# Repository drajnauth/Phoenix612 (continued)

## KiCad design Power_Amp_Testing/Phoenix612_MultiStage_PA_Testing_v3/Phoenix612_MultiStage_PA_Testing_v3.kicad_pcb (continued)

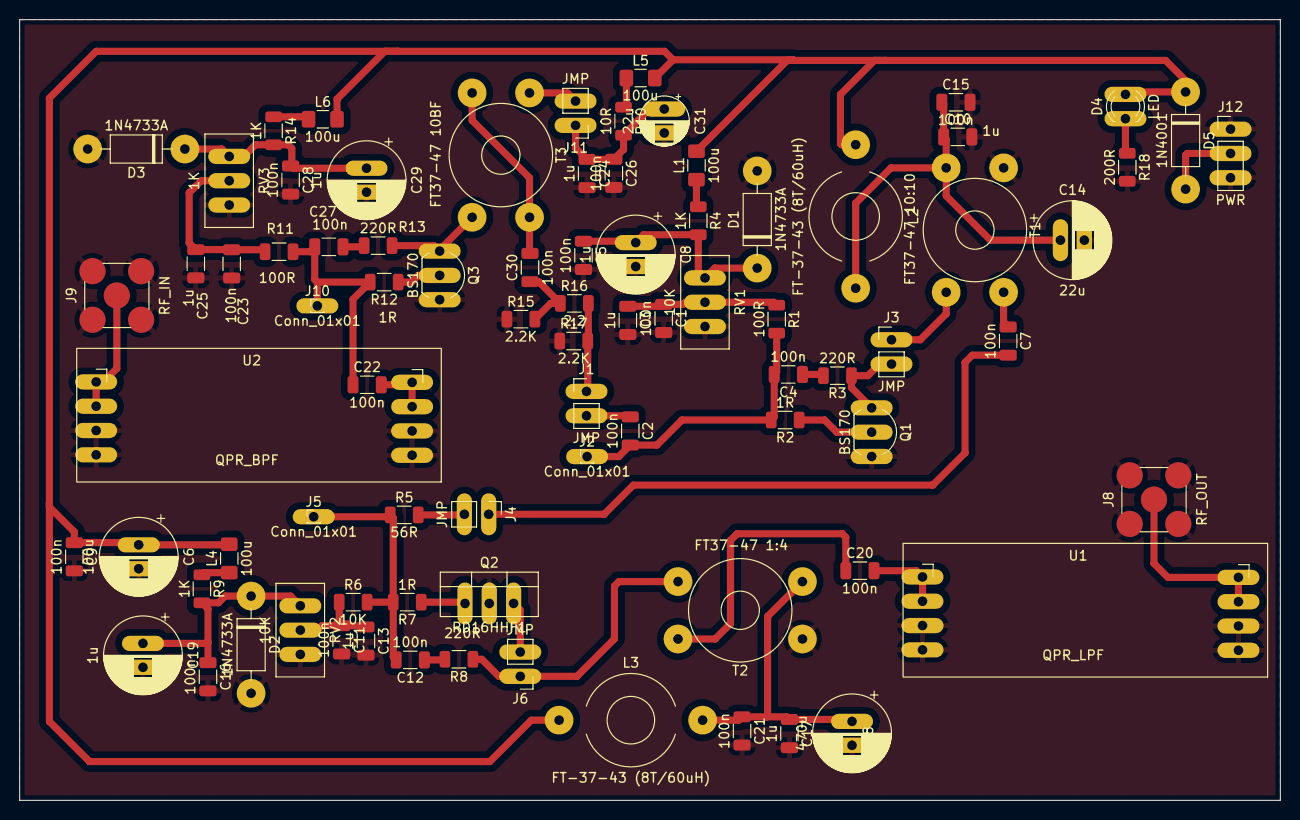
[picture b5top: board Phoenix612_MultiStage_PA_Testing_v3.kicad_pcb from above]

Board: 2 copper layers, 131.8 x 81.6 mm, 82 parts (0 on the bottom side), 44 nets.

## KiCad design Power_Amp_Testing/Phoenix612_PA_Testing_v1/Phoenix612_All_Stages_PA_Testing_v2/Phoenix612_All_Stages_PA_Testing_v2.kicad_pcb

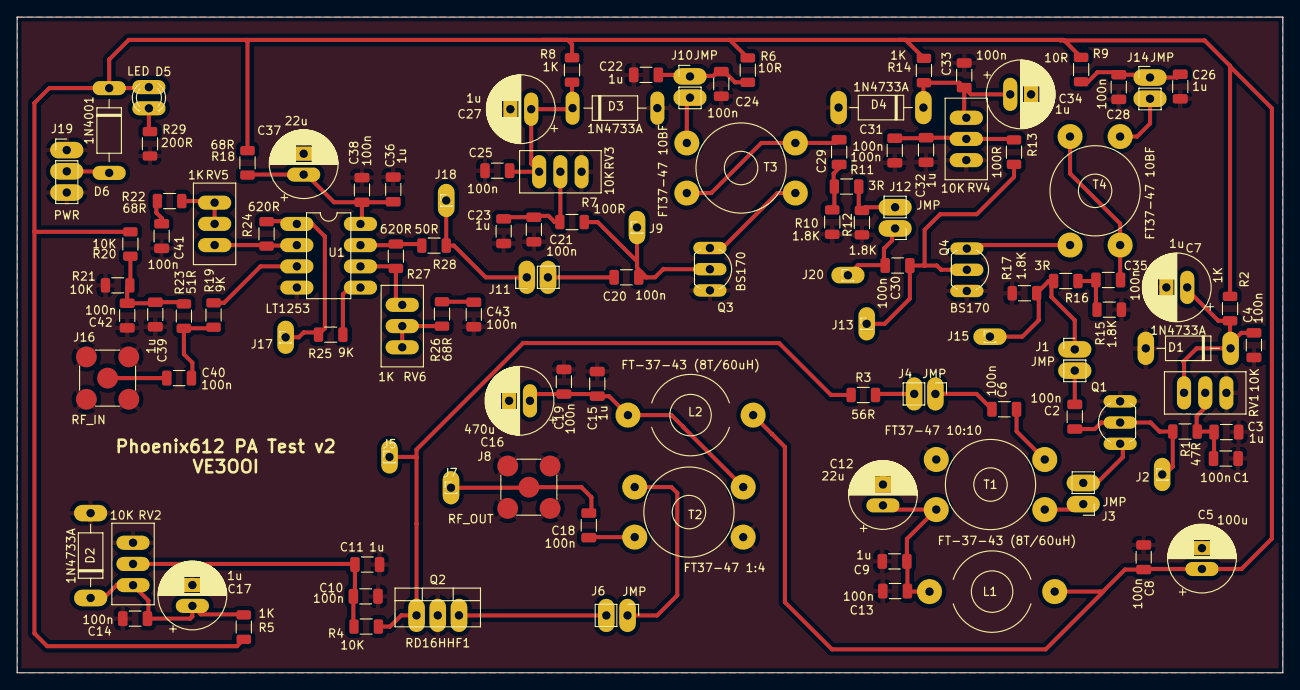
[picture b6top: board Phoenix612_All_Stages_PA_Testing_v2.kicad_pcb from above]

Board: 2 copper layers, 151.7 x 78.6 mm, 115 parts (0 on the bottom side), 57 nets.

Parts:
C1, C2, C4, C6, C8, C10, C13, C14, C18, C19, C20, C21, C24, C25, C28, C29, C30, C31, C33, C35, C38, C40, C41, C42, C43: 100n; C_1206_3216Metric
C3, C9, C11, C15, C22, C23, C26, C32, C36, C39: 1u; C_1206_3216Metric
C5: 100u; CP_Radial_D8.0mm_P2.50mm
C7, C17, C27, C34: 1u; CP_Radial_D8.0mm_P2.50mm
C12, C37: 22u; CP_Radial_D8.0mm_P2.50mm
C16: 470u; CP_Radial_D8.0mm_P2.50mm
D1, D2, D3, D4: 1N4733A; D_DO-41_SOD81_P10.16mm_Horizontal
D5: LED; LED_D3.0mm
D6: 1N4001; D_DO-41_SOD81_P10.16mm_Horizontal
J1, J3, J4, J6, J10, J11, J12, J14: JMP; PinHeader_1x02_P2.54mm_Vertical
J2, J5, J7, J9, J13, J15, J17, J18, J20: Conn_01x01; PinHeader_1x01_P1.00mm_Vertical
J8: RF_OUT; SMA_Amphenol_901-144_Vertical
J16: RF_IN; SMA_Amphenol_901-144_Vertical
J19: PWR; PinHeader_1x03_P2.54mm_Vertical
L1, L2: FT-37-43 (8T/60uH); L_Toroid_Horizontal_D9.5mm_P15.00mm_Diameter10-5mm_Amidon-T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
Q1, Q3, Q4: BS170; TO-92_Inline_Wide
Q2: RD16HHF1; TO-220-3
R1: 47R; R_1206_3216Metric
R2, R5, R8, R14: 1K; R_1206_3216Metric
R3: 56R; R_1206_3216Metric
R4, R20, R21: 10K; R_1206_3216Metric
R6, R9: 10R; R_1206_3216Metric
R7, R13: 100R; R_1206_3216Metric
R10, R12, R15, R17: 1.8K; R_1206_3216Metric
R11, R16: 3R; R_1206_3216Metric
R18, R22, R26: 68R; R_1206_3216Metric
R19, R25: 9K; R_1206_3216Metric
R23: 51R; R_1206_3216Metric
R24, R27: 620R; R_1206_3216Metric
R28: 50R; R_1206_3216Metric
R29: 200R; R_1206_3216Metric
RV1, RV2, RV3, RV4: 10K; Potentiometer_Bourns_3296W_Vertical
RV5, RV6: 1K; Potentiometer_Bourns_3296W_Vertical
T1: FT37-47 10:10; Transformer_Toroid_Horizontal_D10.5mm_Amidon-T37
T2: FT37-47 1:4; Transformer_Toroid_Horizontal_D10.5mm_Amidon-T37
T3, T4: FT37-47 10BF; Transformer_Toroid_Horizontal_D10.5mm_Amidon-T37
U1: LT1253; DIP-8_W7.62mm

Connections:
DRIVER_IN: J11.1, J18.1, R28.2
GND: C1.2, C3.2, C4.2, C5.2, C7.2, C8.2, C9.2, C10.2, C11.2, C12.2, C13.2, C14.2, C15.2, C16.2, C17.2, C19.2, C21.2, C22.2, C23.2, C24.2, C25.2, C26.2, C27.2, C28.2, C31.2, C32.2, C33.2, C34.2, C36.2, C37.2, C38.2, C39.2, C41.2, C42.2, C43.2, D1.2 (A), D2.2 (A), D3.2 (A), D4.2 (A), J8.2 (Ext), J16.2 (Ext), J19.1, J19.3, Q1.3 (S), Q2.2, Q3.3 (S), Q4.3 (S), R10.1, R12.1, R15.1, R17.1, R21.2, R29.2, RV1.1, RV2.1, RV3.1, RV4.1, T1.3 (SB), T2.3 (SB), U1.4 (V-)
M1_12V: C9.1, C12.1, C13.1, L1.2, T1.1 (AA)
M2_12V: C15.1, C16.1, C19.1, L2.2, T2.1 (AA)
unnamed: C1.1, C3.1, R1.1, RV1.2
unnamed: C2.1, J1.2
unnamed: C2.2, J2.1, Q1.2 (G), R1.2
unnamed: C4.1, C7.1, D1.1 (K), R2.2, RV1.3
unnamed: C6.1, T1.4 (SA)
unnamed: C6.2, J4.1
unnamed: C10.1, C11.1, R4.1, RV2.2
unnamed: C14.1, C17.1, D2.1 (K), R5.2, RV2.3
unnamed: C18.1, T2.4 (SA)
unnamed: C18.2, J7.1, J8.1 (In)
unnamed: C20.2, J11.2
unnamed: C21.1, C23.1, R7.1, RV3.2
unnamed: C25.1, C27.1, D3.1 (K), R8.2, RV3.3
unnamed: C29.1, R10.2, R11.1
unnamed: C29.2, T3.1 (AA), T3.4 (SA)
unnamed: C30.1, J13.1, Q4.2 (G), R13.2
unnamed: C30.2, J12.1, J20.1
unnamed: C31.1, C32.1, R13.1, RV4.2
unnamed: C33.1, C34.1, D4.1 (K), R14.2, RV4.3
unnamed: C35.1, R15.2, R16.1
unnamed: C35.2, T4.1 (AA), T4.4 (SA)
unnamed: C36.1, C37.1, C38.1, R18.2, U1.8 (V+)
unnamed: C39.1, C42.1, R20.2, R21.1, R23.2
unnamed: C40.1, J16.1 (In)
unnamed: C40.2, R19.1, R23.1
unnamed: C41.1, R22.2
unnamed: C43.1, R26.2
unnamed: D5.1 (K), R29.1
unnamed: D6.2 (A), J19.2
unnamed: J3.1, T1.2 (AB)
unnamed: J3.2, Q1.1 (D)
unnamed: J4.2, R3.2
unnamed: J5.1, Q2.1, R3.1, R4.2
unnamed: J6.1, T2.2 (AB)
unnamed: J6.2, Q2.3
unnamed: C20.1, J9.1, Q3.2 (G), R7.2
unnamed: J10.2, T3.3 (SB)
unnamed: J12.2, R11.2, R12.2
unnamed: J14.2, T4.3 (SB)
unnamed: J17.1, R24.2, R25.1, U1.1 (OutA)
unnamed: Q3.1 (D), T3.2 (AB)
unnamed: Q4.1 (D), T4.2 (AB)
unnamed: R19.2, U1.3 (InA+)
unnamed: R22.1, RV5.2, RV5.3
unnamed: R24.1, RV5.1, U1.2 (InA-)
unnamed: R25.2, U1.5 (InB+)
unnamed: R26.1, RV6.2, RV6.3
unnamed: R27.1, R28.1, U1.7 (OutB)
unnamed: R27.2, RV6.1, U1.6 (InB-)
PA_IN: J1.1, J15.1, R16.2, R17.2
Q1_12V: C22.1, C24.1, J10.1, R6.2
Q2_12V: C26.1, C28.1, J14.1, R9.2
TX12V: C5.1, C8.1, D5.2 (A), D6.1 (K), L1.1, L2.1, R2.1, R5.1, R6.1, R8.1, R9.1, R14.1, R18.1, R20.1

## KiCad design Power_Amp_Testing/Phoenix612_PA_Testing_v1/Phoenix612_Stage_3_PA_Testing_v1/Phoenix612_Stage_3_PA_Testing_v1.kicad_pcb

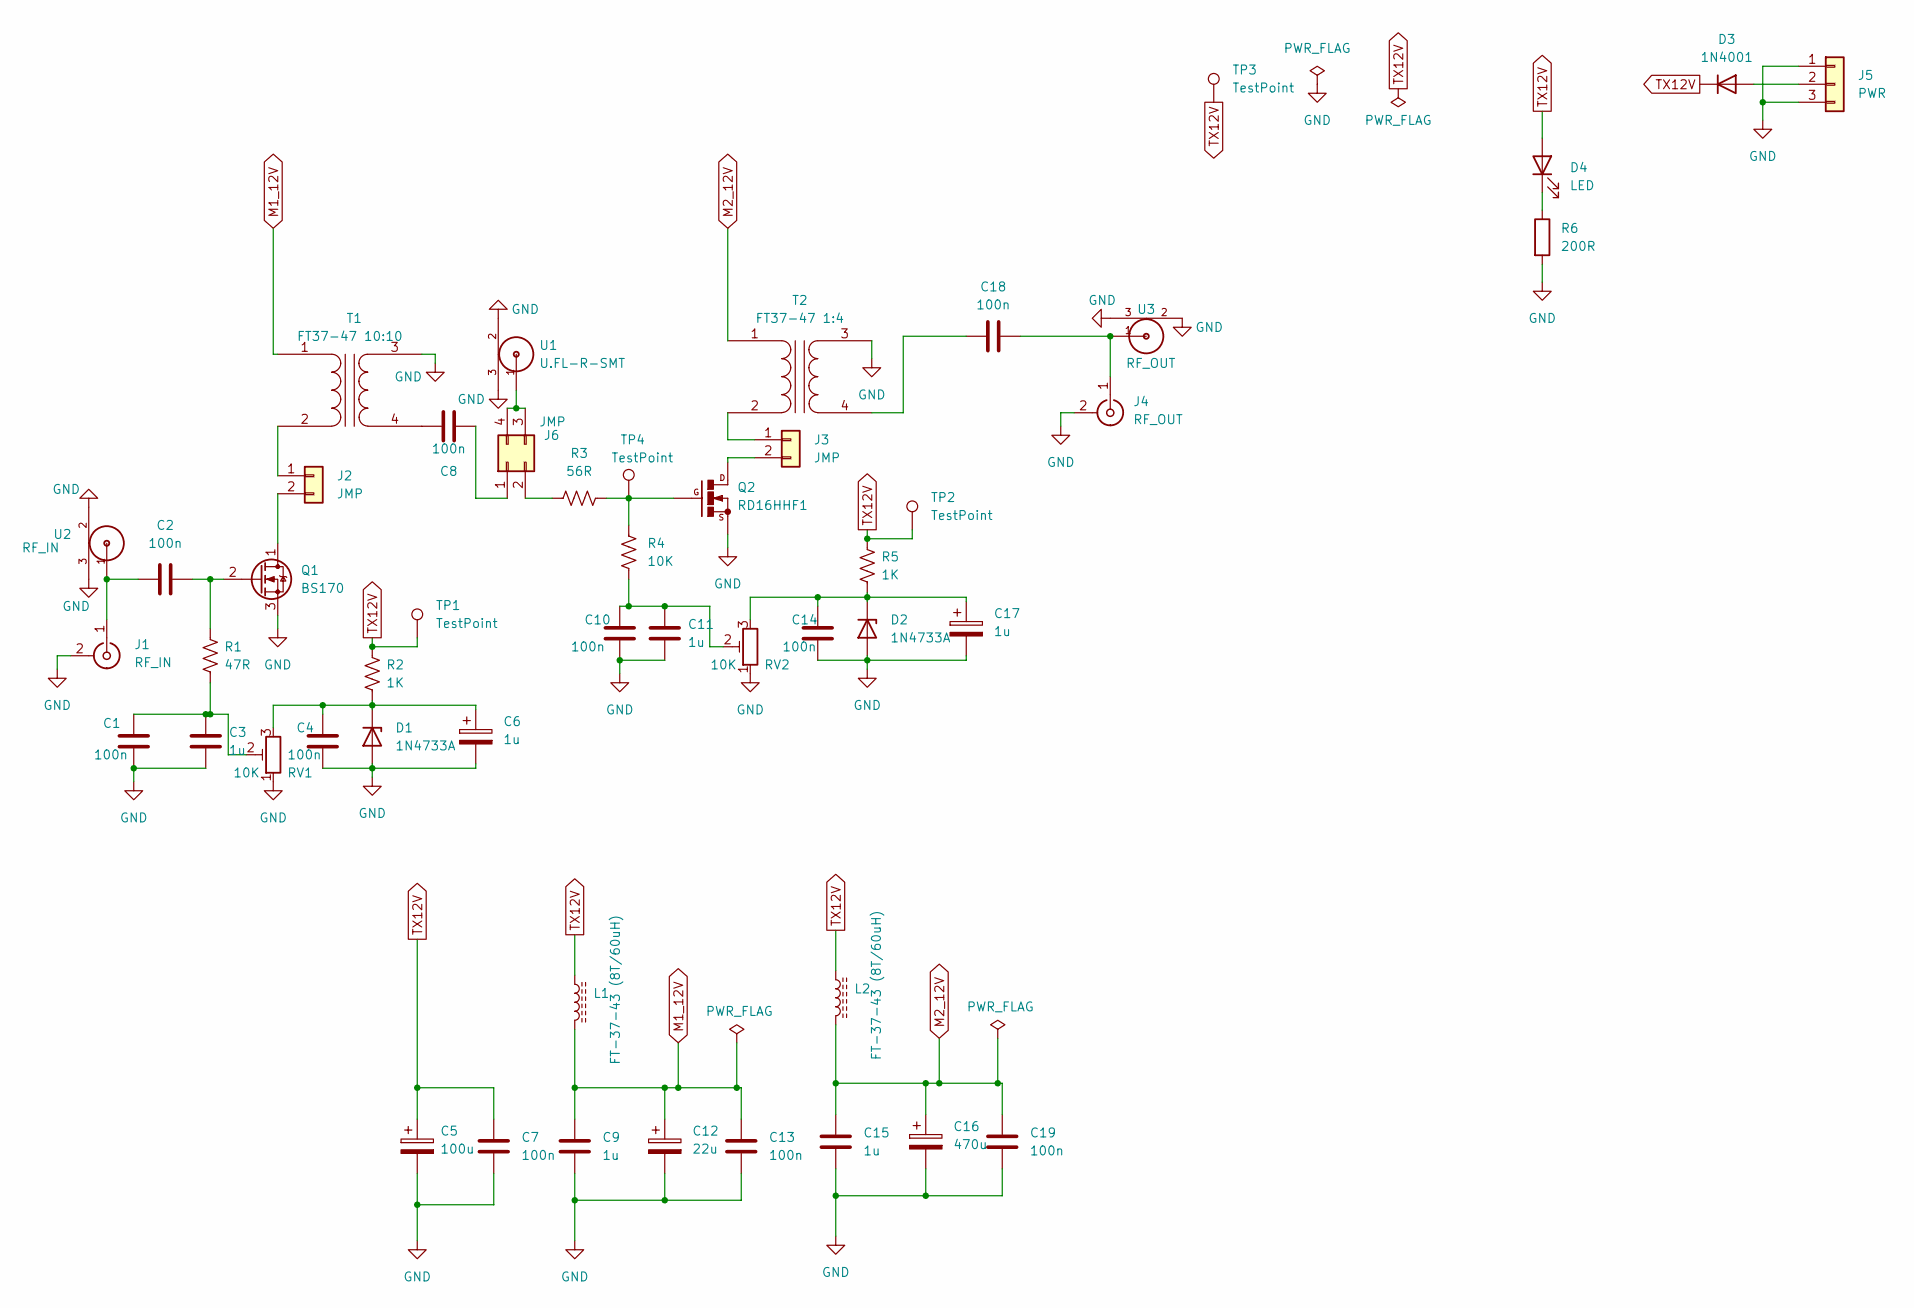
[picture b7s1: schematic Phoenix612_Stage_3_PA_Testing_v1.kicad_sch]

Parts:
C1, C2, C4, C7, C8, C10, C13, C14, C18, C19: 100n; C_1206_3216Metric
C3, C9, C11, C15: 1u; C_1206_3216Metric
C5: 100u; CP_Radial_D8.0mm_P2.50mm
C6, C17: 1u; CP_Radial_D8.0mm_P2.50mm
C12: 22u; CP_Radial_D8.0mm_P2.50mm
C16: 470u; CP_Radial_D8.0mm_P2.50mm
D1, D2: 1N4733A; D_DO-41_SOD81_P10.16mm_Horizontal
D3: 1N4001; D_DO-41_SOD81_P10.16mm_Horizontal
D4: LED; LED_D3.0mm
J1: RF_IN; SMA_Amphenol_901-144_Vertical
J2, J3: JMP; PinHeader_1x02_P2.54mm_Vertical
J4: RF_OUT; SMA_Amphenol_901-144_Vertical
J5: PWR; PinHeader_1x03_P2.54mm_Vertical
J6: JMP; PinHeader_2x02_P2.54mm_Vertical
L1, L2: FT-37-43 (8T/60uH); L_Toroid_Horizontal_D9.5mm_P15.00mm_Diameter10-5mm_Amidon-T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
Q1: BS170; TO-92_Inline
Q2: RD16HHF1; TO-220-3
R1: 47R; R_1206_3216Metric
R2, R5: 1K; R_1206_3216Metric
R3: 56R; R_1206_3216Metric
R4: 10K; R_1206_3216Metric
R6: 200R; R_1206_3216Metric
RV1, RV2: 10K; Potentiometer_Bourns_3296W_Vertical
T1: FT37-47 10:10; Transformer_Toroid_Horizontal_D10.5mm_Amidon-T37
T2: FT37-47 1:4; Transformer_Toroid_Horizontal_D10.5mm_Amidon-T37
TP1, TP2, TP3, TP4: TestPoint; Pin_D0.7mm_L6.5mm_W1.8mm_FlatFork
U1: U.FL-R-SMT
U2: RF_IN; U.FL-R-SMT
U3: RF_OUT; U.FL-R-SMT

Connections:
GND: C1.2, C3.2, C4.2, C5.2, C6.2, C7.2, C9.2, C10.2, C11.2, C12.2, C13.2, C14.2, C15.2, C16.2, C17.2, C19.2, D1.2 (A), D2.2 (A), J1.2 (Ext), J4.2 (Ext), J5.1, J5.3, Q1.3 (S), Q2.2, R6.2, RV1.1, RV2.1, T1.3 (SB), T2.3 (SB), U1.2, U1.3, U2.2, U2.3, U3.2, U3.3
M1_12V: C9.1, C12.1, C13.1, L1.2, T1.1 (AA)
M2_12V: C15.1, C16.1, C19.1, L2.2, T2.1 (AA)
unnamed: C1.1, C3.1, R1.1, RV1.2
unnamed: C2.1, J1.1 (In), U2.1
unnamed: C2.2, Q1.2 (G), R1.2
unnamed: C4.1, C6.1, D1.1 (K), R2.2, RV1.3
unnamed: C8.1, T1.4 (SA)
unnamed: C8.2, J6.1
unnamed: C10.1, C11.1, R4.1, RV2.2
unnamed: C14.1, C17.1, D2.1 (K), R5.2, RV2.3
unnamed: C18.1, T2.4 (SA)
unnamed: C18.2, J4.1 (In), U3.1
unnamed: D3.2 (A), J5.2
unnamed: D4.1 (K), R6.1
unnamed: J2.1, T1.2 (AB)
unnamed: J2.2, Q1.1 (D)
unnamed: J3.1, T2.2 (AB)
unnamed: J3.2, Q2.3
unnamed: J6.2, R3.2
unnamed: J6.3, J6.4, U1.1
unnamed: Q2.1, R3.1, R4.2, TP4.1
TX12V: C5.1, C7.1, D3.1 (K), D4.2 (A), L1.1, L2.1, R2.1, R5.1, TP1.1, TP2.1, TP3.1

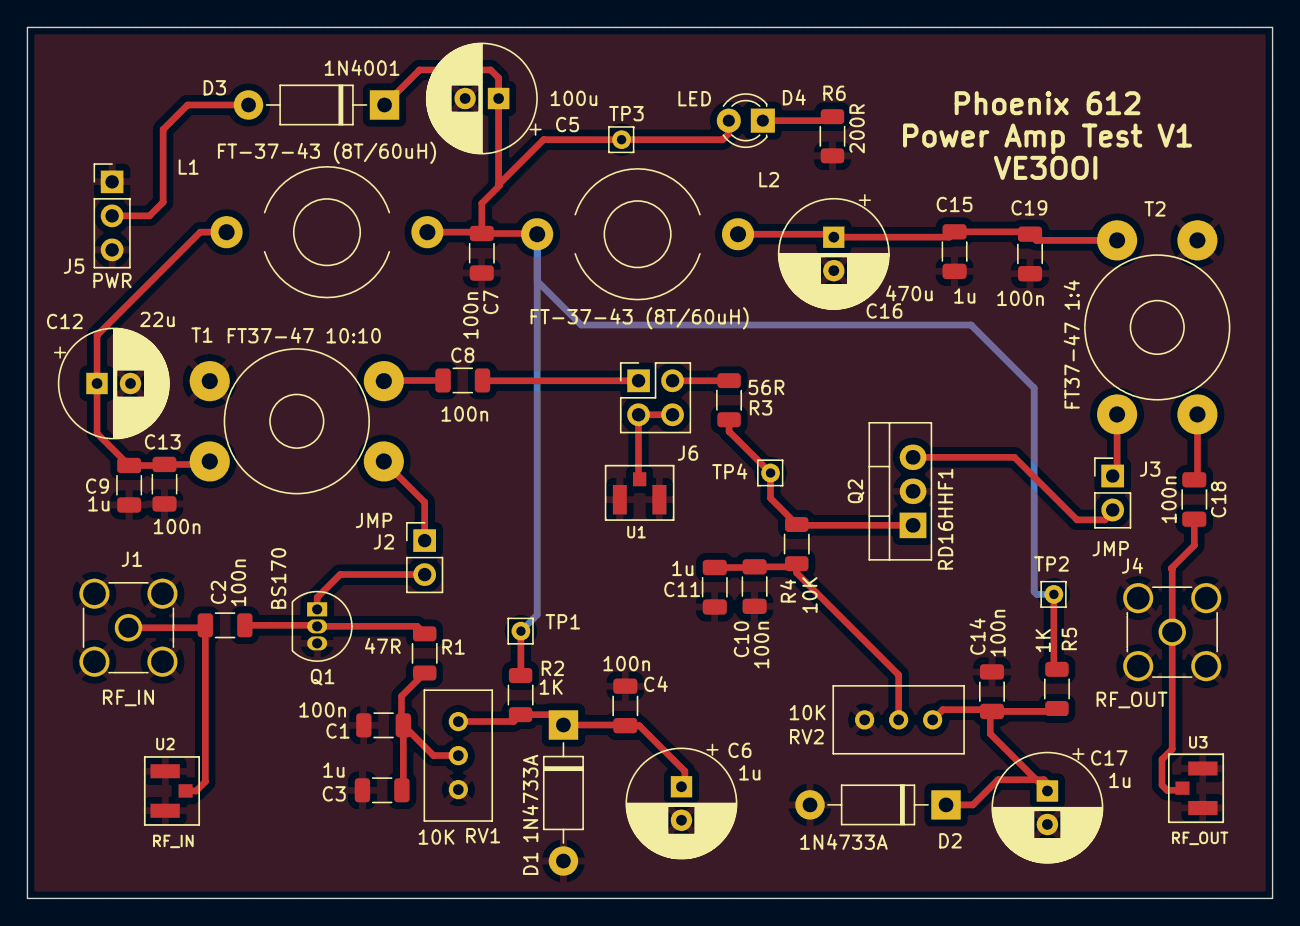
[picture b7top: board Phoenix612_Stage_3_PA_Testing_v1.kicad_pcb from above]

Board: 2 copper layers, 93.0 x 65.0 mm, 50 parts (0 on the bottom side), 23 nets.

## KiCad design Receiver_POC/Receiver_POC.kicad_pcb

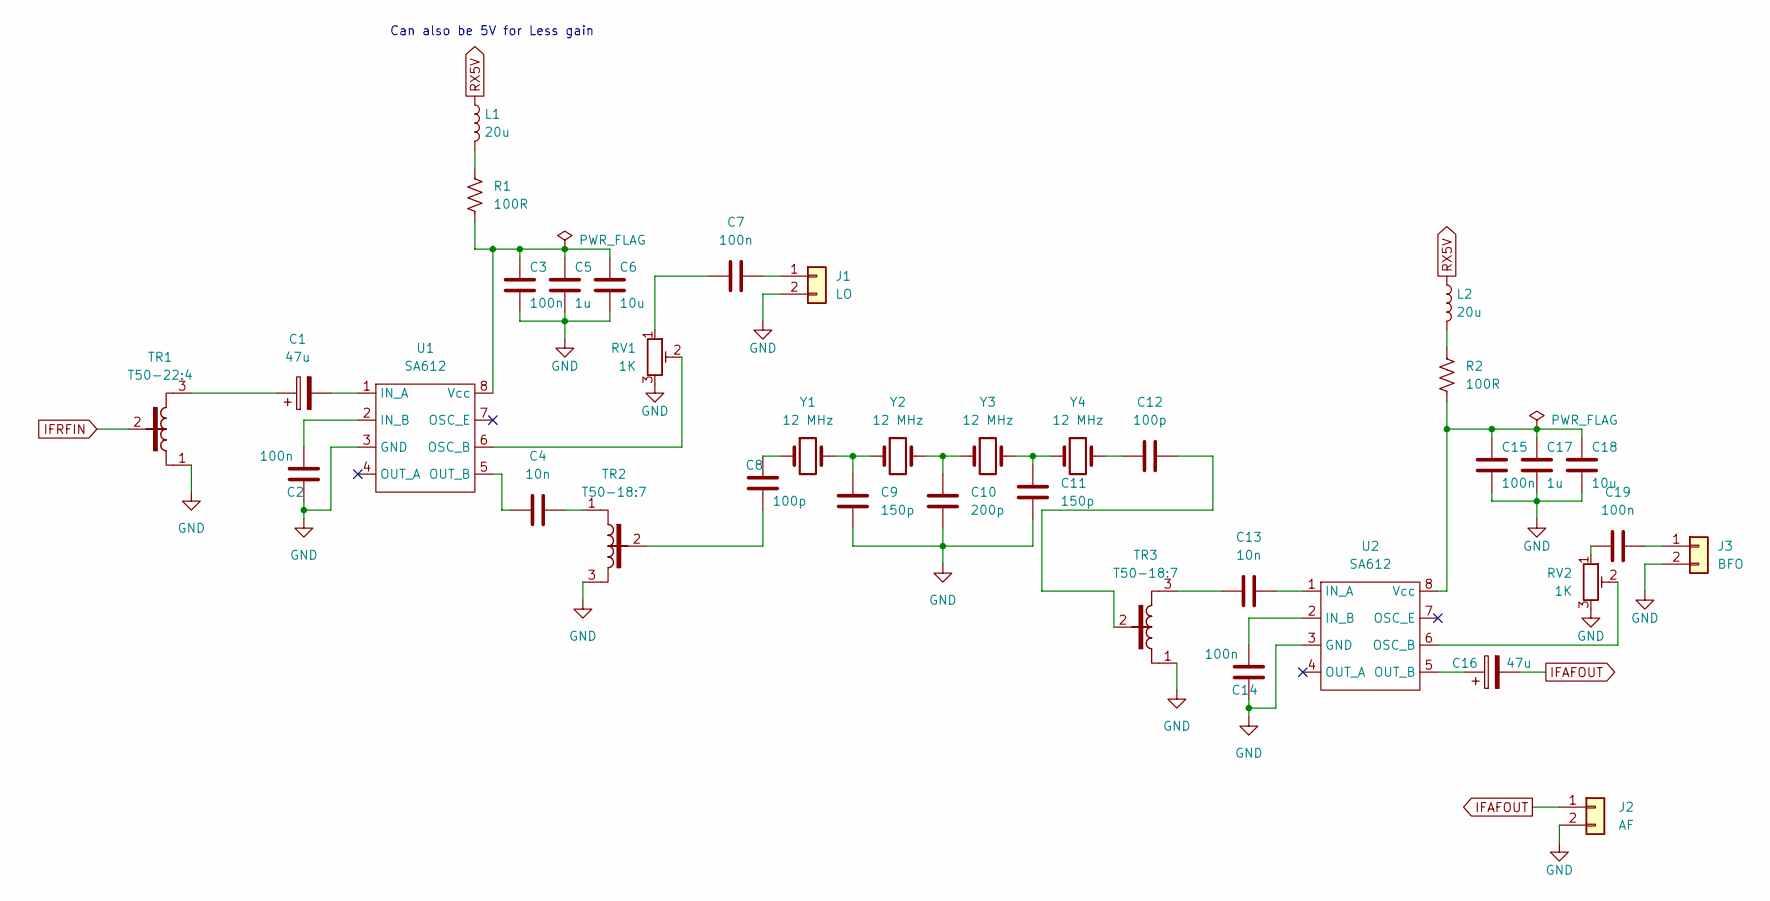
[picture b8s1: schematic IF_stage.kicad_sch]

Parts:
C1, C16: 47u; CP_Radial_D8.0mm_P2.50mm
C2, C3, C7, C14, C15, C19: 100n; C_1206_3216Metric
C4, C13: 10n; C_1206_3216Metric
C5, C17: 1u; C_1206_3216Metric
C6, C18: 10u; C_1206_3216Metric
C8, C12: 100p; C_Disc_D3.4mm_W2.1mm_P2.50mm
C9, C11: 150p; C_Disc_D3.4mm_W2.1mm_P2.50mm
C10: 200p; C_Disc_D3.4mm_W2.1mm_P2.50mm
J1: LO; PinHeader_1x02_P2.54mm_Vertical
J2: AF; PinHeader_1x02_P2.54mm_Vertical
J3: BFO; PinHeader_1x02_P2.54mm_Vertical
L1, L2: 20u; L_1206_3216Metric
R1, R2: 100R; R_1206_3216Metric
RV1, RV2: 1K; Potentiometer_Bourns_3296W_Vertical
TR1: T50-22:4; T50-1Tap-Close
TR2, TR3: T50-18:7; T50-1Tap-Close
U1, U2: SA612; DIP-8_W7.62mm_Socket
Y1, Y2, Y3, Y4: 12 MHz; Crystal_HC49-4H_Vertical

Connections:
GND: C2.2, C3.2, C5.2, C6.2, C9.2, C10.2, C11.2, C14.2, C15.2, C17.2, C18.2, J1.2, J2.2, J3.2, RV1.3, RV2.3, TR1.1, TR2.3, TR3.1, U1.3 (GND), U2.3 (GND); also elsewhere on the board
IFAFOUT: C16.2, J2.1
IFRFIN: TR1.2; also elsewhere on the board
unnamed: C1.1, TR1.3
unnamed: C1.2, U1.1 (IN_A)
unnamed: C2.1, U1.2 (IN_B)
unnamed: C3.1, C5.1, C6.1, R1.2, U1.8 (Vcc)
unnamed: C4.1, U1.5 (OUT_B)
unnamed: C4.2, TR2.1
unnamed: C7.1, J1.1
unnamed: C7.2, RV1.1
unnamed: C8.1, TR2.2
unnamed: C8.2, Y1.1
unnamed: C9.1, Y1.2, Y2.1
unnamed: C10.1, Y2.2, Y3.1
unnamed: C11.1, Y3.2, Y4.1
unnamed: C12.1, Y4.2
unnamed: C12.2, TR3.2
unnamed: C13.1, TR3.3
unnamed: C13.2, U2.1 (IN_A)
unnamed: C14.1, U2.2 (IN_B)
unnamed: C15.1, C17.1, C18.1, R2.2, U2.8 (Vcc)
unnamed: C16.1, U2.5 (OUT_B)
unnamed: C19.1, J3.1
unnamed: C19.2, RV2.1
unnamed: L1.2, R1.1
unnamed: L2.2, R2.1
unnamed: RV1.2, U1.6 (OSC_B)
unnamed: RV2.2, U2.6 (OSC_B)
RX5V: L1.1, L2.1; also elsewhere on the board

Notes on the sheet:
Can also be 5V for Less gain

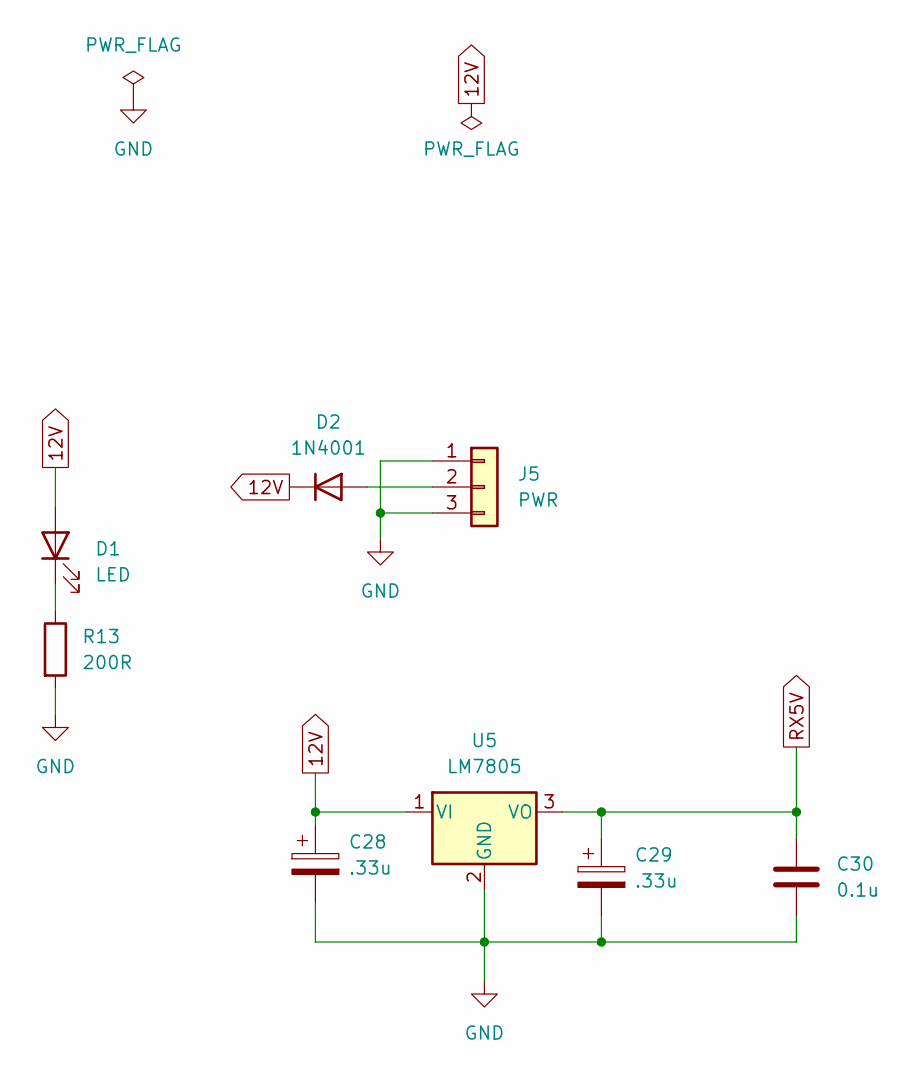
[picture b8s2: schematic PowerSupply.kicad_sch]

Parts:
C28, C29: .33u; CP_Radial_D8.0mm_P2.50mm
C30: 0.1u; C_1206_3216Metric
D1: LED; LED_D3.0mm
D2: 1N4001; D_DO-41_SOD81_P10.16mm_Horizontal
J5: PWR; PinHeader_1x03_P2.54mm_Vertical
R13: 200R; R_1206_3216Metric
U5: LM7805; TO-220-3_Vertical

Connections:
12V: C28.1, D1.2 (A), D2.1 (K), U5.1 (VI)
GND: C28.2, C29.2, C30.2, J5.1, J5.3, R13.2, U5.2 (GND); also elsewhere on the board
unnamed: D1.1 (K), R13.1
unnamed: D2.2 (A), J5.2
RX5V: C29.1, C30.1, U5.3 (VO); also elsewhere on the board

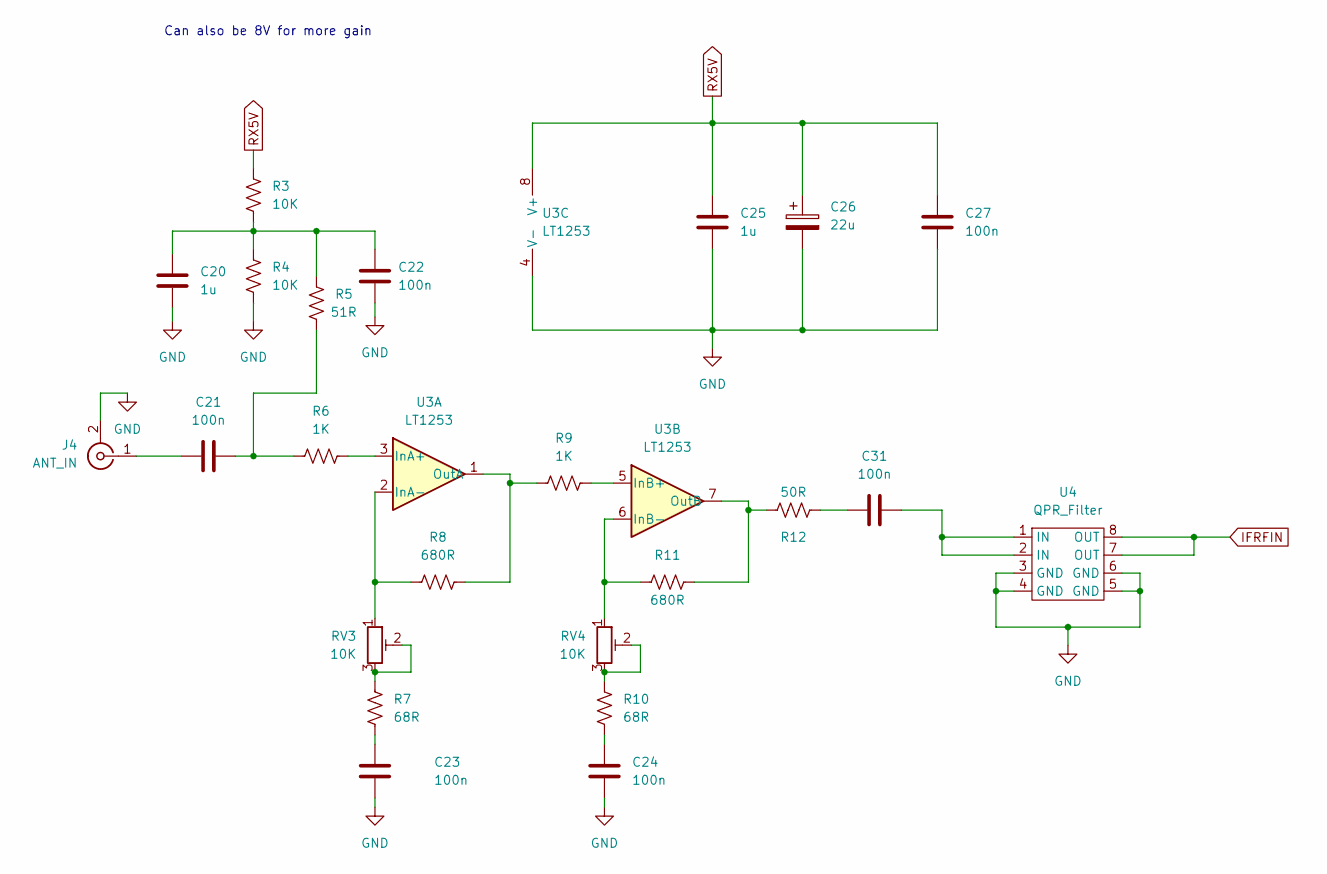
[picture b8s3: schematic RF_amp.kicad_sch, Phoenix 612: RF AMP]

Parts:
C20, C25: 1u; C_1206_3216Metric
C21, C22, C23, C24, C27, C31: 100n; C_1206_3216Metric
C26: 22u; CP_Radial_D8.0mm_P2.50mm
J4: ANT_IN; SMA_Amphenol_901-144_Vertical
R3, R4: 10K; R_1206_3216Metric
R5: 51R; R_1206_3216Metric
R6, R9: 1K; R_1206_3216Metric
R7, R10: 68R; R_1206_3216Metric
R8, R11: 680R; R_1206_3216Metric
R12: 50R; R_1206_3216Metric
RV3, RV4: 10K; Potentiometer_Bourns_3296W_Vertical
U3: LT1253; DIP-8_W7.62mm
U4: QPR_Filter; QRPLabs_Filter_TH

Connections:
GND: C20.2, C22.2, C23.2, C24.2, C25.2, C26.2, C27.2, J4.2 (Ext), R4.2, U3.4 (V-), U4.3 (GND), U4.4 (GND), U4.5 (GND), U4.6 (GND); also elsewhere on the board
IFRFIN: U4.7 (OUT), U4.8 (OUT); also elsewhere on the board
unnamed: C20.1, C22.1, R3.2, R4.1, R5.2
unnamed: C21.1, J4.1 (In)
unnamed: C21.2, R5.1, R6.1
unnamed: C23.1, R7.2
unnamed: C24.1, R10.2
unnamed: R6.2, U3.3 (InA+)
unnamed: R7.1, RV3.2, RV3.3
unnamed: R8.1, RV3.1, U3.2 (InA-)
unnamed: R8.2, R9.1, U3.1 (OutA)
unnamed: R9.2, U3.5 (InB+)
unnamed: R10.1, RV4.2, RV4.3
unnamed: R11.1, R12.1, U3.7 (OutB)
unnamed: R11.2, RV4.1, U3.6 (InB-)
unnamed: C31.1, R12.2
unnamed: C31.2, U4.1 (IN), U4.2 (IN)
RX5V: C25.1, C26.1, C27.1, R3.1, U3.8 (V+); also elsewhere on the board

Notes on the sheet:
Can also be 8V for more gain

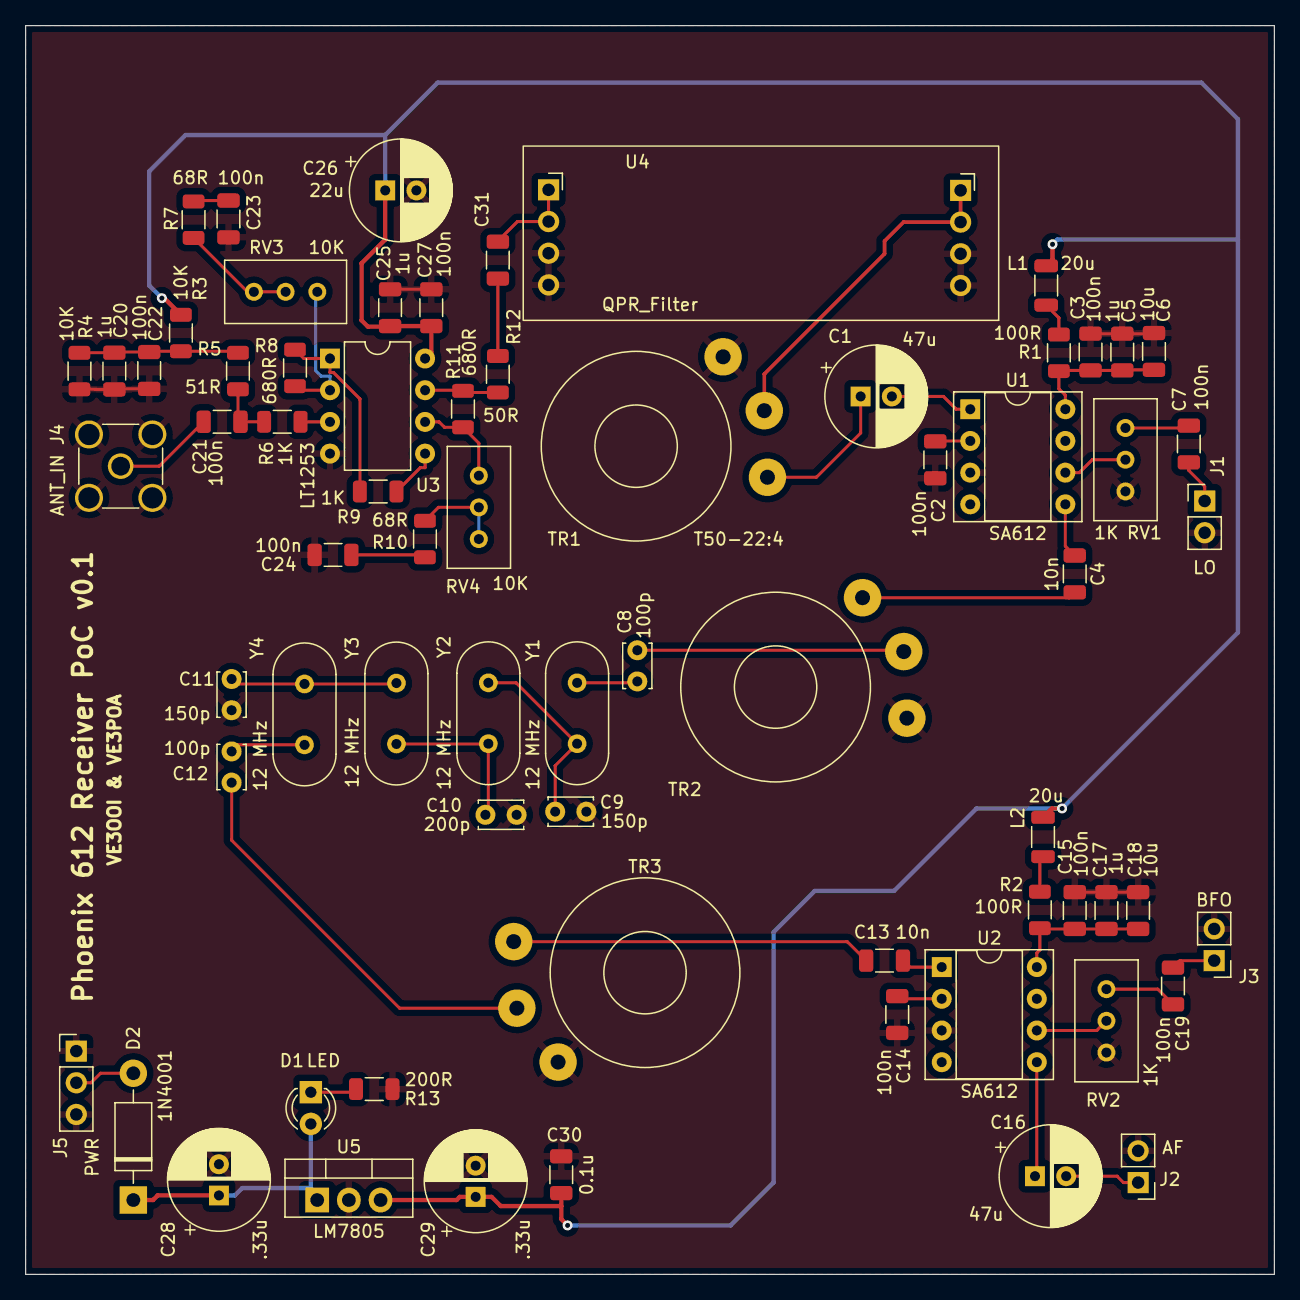
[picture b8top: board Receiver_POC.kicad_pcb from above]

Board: 2 copper layers, 100.1 x 100.1 mm, 69 parts (0 on the bottom side), 48 nets.
